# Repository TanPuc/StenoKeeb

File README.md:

# StenoKeeb
A stenokeyboard project

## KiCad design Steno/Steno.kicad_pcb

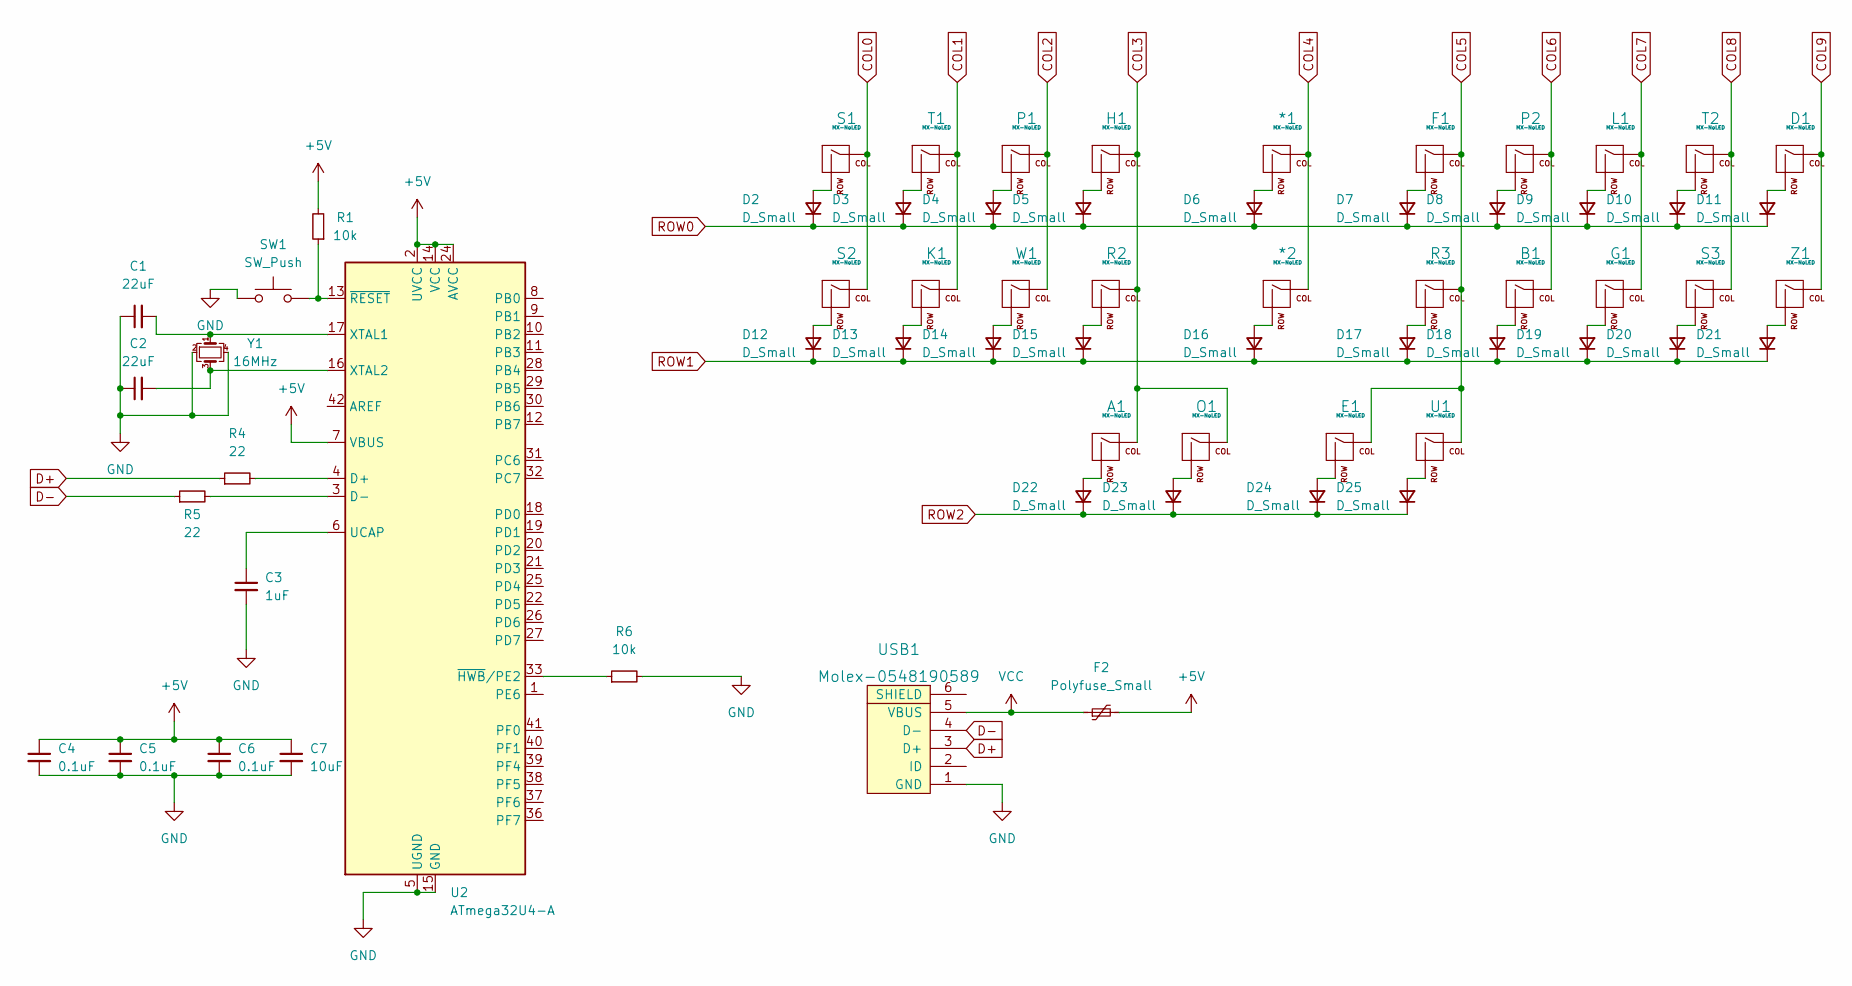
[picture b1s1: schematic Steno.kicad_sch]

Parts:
*1, *2: MX-NoLED; MX-1U
A1: MX-NoLED; MX-1U
B1: MX-NoLED; MX-1U
C1, C2: 22uF; C_0805_2012Metric
C3: 1uF; C_0805_2012Metric
C4, C5, C6: 0.1uF; C_0805_2012Metric
C7: 10uF; C_0805_2012Metric
D1: MX-NoLED; MX-1U
D2, D3, D4, D5, D6, D7, D8, D9, D10, D11, D12, D13, D14, D15, D16, D17, D18, D19, D20, D21, D22, D23, D24, D25: D_Small; D_SOD-123
E1: MX-NoLED; MX-1U
F1: MX-NoLED; MX-1U
F2: Polyfuse_Small; Fuse_1206_3216Metric
G1: MX-NoLED; MX-1U
H1: MX-NoLED; MX-1U
K1: MX-NoLED; MX-1U
L1: MX-NoLED; MX-1U
O1: MX-NoLED; MX-1U
P1, P2: MX-NoLED; MX-1U
R1, R6: 10k; R_0805_2012Metric
R2, R3: MX-NoLED; MX-1U
R4, R5: 22; R_0805_2012Metric
S1, S2, S3: MX-NoLED; MX-1U
SW1: SW_Push; SKQG-1155865
T1, T2: MX-NoLED; MX-1U
U1: MX-NoLED; MX-1U
U2: ATmega32U4-A; TQFP-44_10x10mm_P0.8mm
USB1: Molex-0548190589
W1: MX-NoLED; MX-1U
Y1: 16MHz; Crystal_SMD_3225-4Pin_3.2x2.5mm
Z1: MX-NoLED; MX-1U

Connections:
+5V: C4.1, C5.1, C6.1, C7.1, F2.2, R1.2, U2.2 (UVCC), U2.7 (VBUS), U2.14 (VCC), U2.24 (AVCC), U2.34 (VCC), U2.44 (AVCC)
COL0: S1.1 (COL), S2.1 (COL)
COL1: K1.1 (COL), T1.1 (COL)
COL2: P1.1 (COL), W1.1 (COL)
COL3: A1.1 (COL), H1.1 (COL), O1.1 (COL), R2.1 (COL)
COL4: *1.1 (COL), *2.1 (COL)
COL5: E1.1 (COL), F1.1 (COL), R3.1 (COL), U1.1 (COL)
COL6: B1.1 (COL), P2.1 (COL)
COL7: G1.1 (COL), L1.1 (COL)
COL8: S3.1 (COL), T2.1 (COL)
COL9: D1.1 (COL), Z1.1 (COL)
D+: R4.1, USB1.3 (D+)
D-: R5.1, USB1.4 (D-)
GND: C1.1, C2.1, C3.2, C4.2, C5.2, C6.2, C7.2, R6.2, SW1.1, U2.5 (UGND), U2.15 (GND), U2.23 (GND), U2.35 (GND), U2.43 (GND), USB1.1 (GND), Y1.2, Y1.4
unnamed: *1.2 (ROW), D6.2 (A)
unnamed: *2.2 (ROW), D16.2 (A)
unnamed: A1.2 (ROW), D22.2 (A)
unnamed: B1.2 (ROW), D18.2 (A)
unnamed: C1.2, U2.17 (XTAL1), Y1.1
unnamed: C2.2, U2.16 (XTAL2), Y1.3
unnamed: C3.1, U2.6 (UCAP)
unnamed: D1.2 (ROW), D11.2 (A)
unnamed: D24.2 (A), E1.2 (ROW)
unnamed: D7.2 (A), F1.2 (ROW)
unnamed: D19.2 (A), G1.2 (ROW)
unnamed: D5.2 (A), H1.2 (ROW)
unnamed: D13.2 (A), K1.2 (ROW)
unnamed: D9.2 (A), L1.2 (ROW)
unnamed: D23.2 (A), O1.2 (ROW)
unnamed: D4.2 (A), P1.2 (ROW)
unnamed: D8.2 (A), P2.2 (ROW)
unnamed: R1.1, SW1.2, U2.13 (~RESET)
unnamed: D15.2 (A), R2.2 (ROW)
unnamed: D17.2 (A), R3.2 (ROW)
unnamed: R4.2, U2.4 (D+)
unnamed: R5.2, U2.3 (D-)
unnamed: R6.1, U2.33 (~HWB/PE2)
unnamed: D2.2 (A), S1.2 (ROW)
unnamed: D12.2 (A), S2.2 (ROW)
unnamed: D20.2 (A), S3.2 (ROW)
unnamed: D3.2 (A), T1.2 (ROW)
unnamed: D10.2 (A), T2.2 (ROW)
unnamed: D25.2 (A), U1.2 (ROW)
unnamed: D14.2 (A), W1.2 (ROW)
unnamed: D21.2 (A), Z1.2 (ROW)
ROW0: D2.1 (K), D3.1 (K), D4.1 (K), D5.1 (K), D6.1 (K), D7.1 (K), D8.1 (K), D9.1 (K), D10.1 (K), D11.1 (K)
ROW1: D12.1 (K), D13.1 (K), D14.1 (K), D15.1 (K), D16.1 (K), D17.1 (K), D18.1 (K), D19.1 (K), D20.1 (K), D21.1 (K)
ROW2: D22.1 (K), D23.1 (K), D24.1 (K), D25.1 (K)
VCC: F2.1, USB1.5 (VBUS)

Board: 2 copper layers, 64 parts (0 on the bottom side), 49 nets, no tracks yet.

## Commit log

2023-01-01 Creating files
2023-01-03 basic changes
2023-01-03 Small push 2
